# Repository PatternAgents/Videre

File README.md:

Videre
=============

PatternAgents Videre - LCD Shield with Cortex-M0

[  
*PatternAgents Videre*](http://www.patternagents.com/projects/Videre.html)

The PatternAgents Videre uses an ARM Cortex-M0 based Programmable System-on-Chip (PSoC4) 
to control a 16x2 Character LCD with color backlighting. The PSoC4  can read read inputs from sensors, 
switches, potentiometers, or other analog inputs and display those sensors directly on the LCD in
standalone mode. Or you can use it as an Arduino Shield, with either I2C,, UART, or SPI interface.

Features:

        16 Character x 2 Line Display

        Color LED Backlighting
	
        Selectable 3.3Volt or 5.0Volt Operation
	
        UART, I2C, SPI Interface Selectable
	
        Use as Arduino Shield or as a Standalone Display
	
        CapSense Slider Bar (optional)      

	Arduino Uno/Leonardo/Mega/Due Compatible Shield

You can read more about the PSoC4 Integrated Circuit used here : http://www.cypress.com/?mpn=CY8C4245AXI-483

[  
*Licensing CC BY-NC-SA 4.0*](http://creativecommons.org/licenses/by-nc-sa/4.0/)

PatternAgents uses the increasingly popular business model called "Dual Licensing" 
in which both the open source software distribution mechanism and traditional commercial software distribution models are combined.

Open Source Projects:        

If you are developing and distributing open source applications under the Creative Commons CC BY-NC-SA 4.0, 
as published by the Creative Commons Foundation, then you are free to use the PatternAgents hardware/software under the CC BY-NC-SA 4.0 license. 
Please note that CC BY-NC-SA 4.0 requires that all modifications to the original code as well as all Derivative Works 
must also be released under the terms of the CC BY-NC-SA 4.0 license.

Closed Source Projects:

If you are developing and distributing traditional closed source or commercial applications, 
you must purchase a PatternAgents commercial use license, 
which is specifically designed for users interested in retaining the proprietary status of their designs and code. 
All PatternAgents commercial licenses expressly supersede the CC BY-NC-SA 4.0 license. 
This means that when you license the PatternAgents software under a commercial license, 
you specifically do not use the software under the CC BY-NC-SA 4.0 license and therefore you are not subject to any of its terms.
        
If you would like to use our designs for your own personal or educational use, have at it! 

Our public design repository is available at <a href="https://github.com/patternagents">Github</a>.

If you would like to produce our designs for commercial use, or as products for sale, 
please contact us to arrange for a Commercial Use license. We have many other designs, 
as well as options and extras that are not released publicly. 
We will also customize designs, firmware, and software for a reasonable fee, just contact us to discuss your requirements.

THIS SOFTWARE IS PROVIDED BY THE CONTRIBUTORS "AS IS" AND WITHOUT ANY EXPRESS OR IMPLIED WARRANTIES, 
INCLUDING, BUT NOT LIMITED TO, THE IMPLIED WARRANTIES OF MERCHANTABILITY AND FITNESS FOR A PARTICULAR PURPOSE ARE DISCLAIMED. 
IN NO EVENT SHALL THE COPYRIGHT OWNER OR CONTRIBUTORS BE LIABLE FOR ANY DIRECT, INDIRECT, INCIDENTAL, SPECIAL, EXEMPLARY, 
OR CONSEQUENTIAL DAMAGES (INCLUDING, BUT NOT LIMITED TO, PROCUREMENT OF SUBSTITUTE GOODS OR SERVICES; LOSS OF USE, DATA, 
OR PROFITS; OR BUSINESS INTERRUPTION) HOWEVER CAUSED AND ON ANY THEORY OF LIABILITY, WHETHER IN CONTRACT, 
STRICT LIABILITY, OR TORT (INCLUDING NEGLIGENCE OR OTHERWISE) ARISING IN ANY WAY OUT OF THE USE OF THIS SOFTWARE, 
EVEN IF ADVISED OF THE POSSIBILITY OF SUCH DAMAGE. 

-------------------------------------------------------------------------------------------

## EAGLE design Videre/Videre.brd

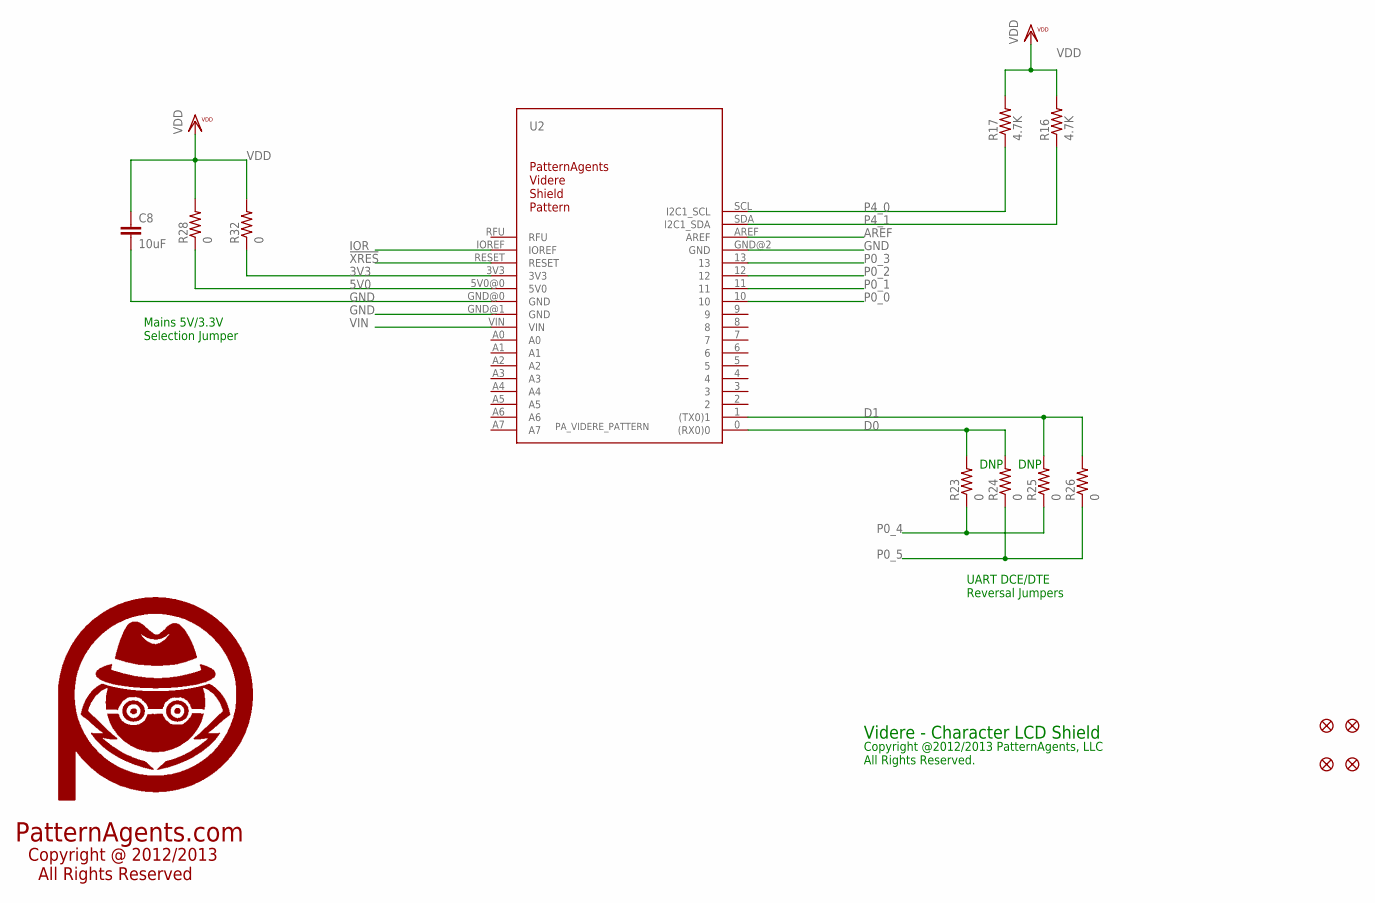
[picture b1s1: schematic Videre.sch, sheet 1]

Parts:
C8: 10uF; 1210
FID1, FID2, FID3, FID4: FIDUCIAL1.5X3; FIDUCIAL-1.5X3
R16, R17: 4.7K; R0603
R23, R24, R25, R26: 0; 0603-RES
R28, R32: 0; 0603-RES@1
U2: PA_VIDERE_PATTERN
U$3: PA_LOGO_SYMLARGE; PA_LOGO_AGENT_LRG_SYM

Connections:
3V3: R32.1, U2.3V3
5V0: R28.1, U2.5V0@0 (5V0)
!XRES: U2.RESET; also elsewhere on the board
AREF: U2.AREF
D0: R23.2, R24.2, U2.0 ((RX0)0)
D1: R25.2, R26.2, U2.1 ((TX0)1)
GND: C8.2, U2.GND@0 (GND), U2.GND@1 (GND), U2.GND@2 (GND); also elsewhere on the board
IOR: U2.IOREF
P0_0: U2.10; also elsewhere on the board
P0_1: U2.11; also elsewhere on the board
P0_2: U2.12; also elsewhere on the board
P0_3: U2.13; also elsewhere on the board
P0_4: R23.1, R25.1; also elsewhere on the board
P0_5: R24.1, R26.1; also elsewhere on the board
P4_0: R17.1, U2.SCL (I2C1_SCL); also elsewhere on the board
P4_1: R16.1, U2.SDA (I2C1_SDA); also elsewhere on the board
RFU: U2.RFU
VDD: C8.1, R16.2, R17.2, R28.2, R32.2; also elsewhere on the board
VIN: U2.VIN; also elsewhere on the board

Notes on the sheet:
DNP
UART DCE/DTE Reversal Jumpers
Mains 5V/3.3V Selection Jumper
PatternAgents.com
Copyright @ 2012/2013 All Rights Reserved
Videre - Character LCD Shield
Copyright @2012/2013 PatternAgents, LLC All Rights Reserved.

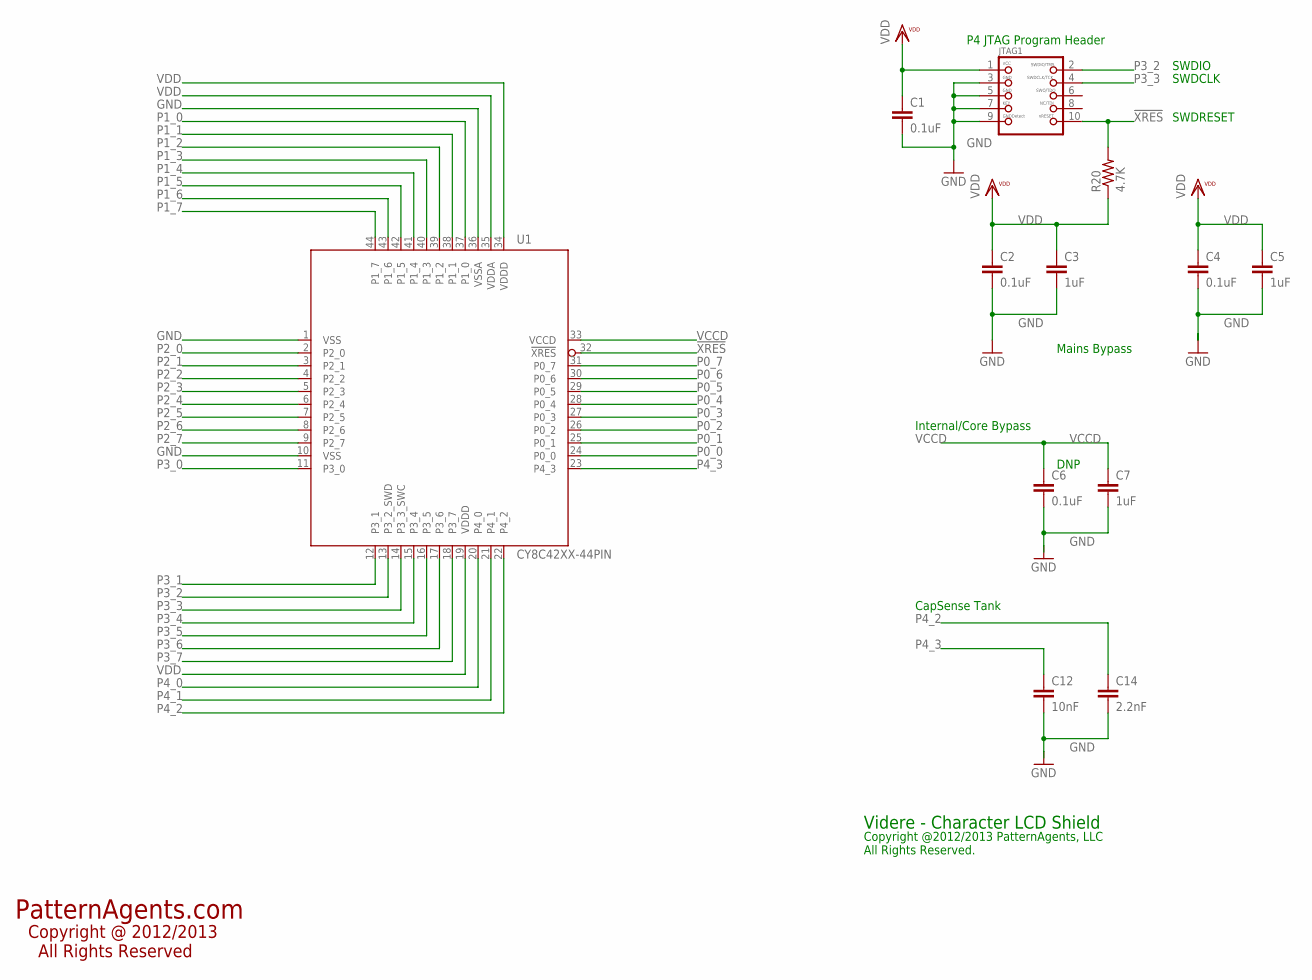
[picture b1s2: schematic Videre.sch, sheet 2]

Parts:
C1, C2, C4, C6: 0.1uF; 0603-CAP
C3, C5, C7: 1uF; 0603-CAP
C12: 10nF; 0603-CAP
C14: 2.2nF; 0603-CAP
JTAG1: JTAG-CORTEXM3; 2X05_1.27MM_SMT
R20: 4.7K; 0603-RES
U1: CY8C42XX-44PIN; TQFP-10X10-44

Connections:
!XRES: JTAG1.10, R20.2, U1.32 (!XRES); also elsewhere on the board
GND: C1.2, C2.2, C3.2, C4.2, C5.2, C6.2, C7.2, C12.2, C14.2, JTAG1.3, JTAG1.5, JTAG1.7, JTAG1.9, U1.1 (VSS), U1.10 (VSS), U1.36 (VSSA); also elsewhere on the board
P0_0: U1.24 (P0_0); also elsewhere on the board
P0_1: U1.25 (P0_1); also elsewhere on the board
P0_2: U1.26 (P0_2); also elsewhere on the board
P0_3: U1.27 (P0_3); also elsewhere on the board
P0_4: U1.28 (P0_4); also elsewhere on the board
P0_5: U1.29 (P0_5); also elsewhere on the board
P0_6: U1.30 (P0_6); also elsewhere on the board
P0_7: U1.31 (P0_7); also elsewhere on the board
P1_0: U1.37 (P1_0); also elsewhere on the board
P1_1: U1.38 (P1_1); also elsewhere on the board
P1_2: U1.39 (P1_2); also elsewhere on the board
P1_3: U1.40 (P1_3); also elsewhere on the board
P1_4: U1.41 (P1_4); also elsewhere on the board
P1_5: U1.42 (P1_5); also elsewhere on the board
P1_6: U1.43 (P1_6); also elsewhere on the board
P1_7: U1.44 (P1_7); also elsewhere on the board
P2_0: U1.2 (P2_0); also elsewhere on the board
P2_1: U1.3 (P2_1); also elsewhere on the board
P2_2: U1.4 (P2_2); also elsewhere on the board
P2_3: U1.5 (P2_3); also elsewhere on the board
P2_4: U1.6 (P2_4); also elsewhere on the board
P2_5: U1.7 (P2_5); also elsewhere on the board
P2_6: U1.8 (P2_6); also elsewhere on the board
P2_7: U1.9 (P2_7); also elsewhere on the board
P3_0: U1.11 (P3_0); also elsewhere on the board
P3_1: U1.12 (P3_1); also elsewhere on the board
P3_2: JTAG1.2, U1.13 (P3_2_SWD)
P3_3: JTAG1.4, U1.14 (P3_3_SWC)
P3_4: U1.15 (P3_4); also elsewhere on the board
P3_5: U1.16 (P3_5); also elsewhere on the board
P3_6: U1.17 (P3_6); also elsewhere on the board
P3_7: U1.18 (P3_7); also elsewhere on the board
P4_0: U1.20 (P4_0); also elsewhere on the board
P4_1: U1.21 (P4_1); also elsewhere on the board
P4_2: C14.1, U1.22 (P4_2)
P4_3: C12.1, U1.23 (P4_3)
VCCD: C6.1, C7.1, U1.33 (VCCD)
VDD: C1.1, C2.1, C3.1, C4.1, C5.1, JTAG1.1, R20.1, U1.19 (VDDD), U1.34 (VDDD), U1.35 (VDDA); also elsewhere on the board

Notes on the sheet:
SWDIO
SWDCLK
SWDRESET
P4 JTAG Program Header
DNP
CapSense Tank
Internal/Core Bypass
Mains Bypass
Videre - Character LCD Shield
Copyright @2012/2013 PatternAgents, LLC All Rights Reserved.
PatternAgents.com
Copyright @ 2012/2013 All Rights Reserved

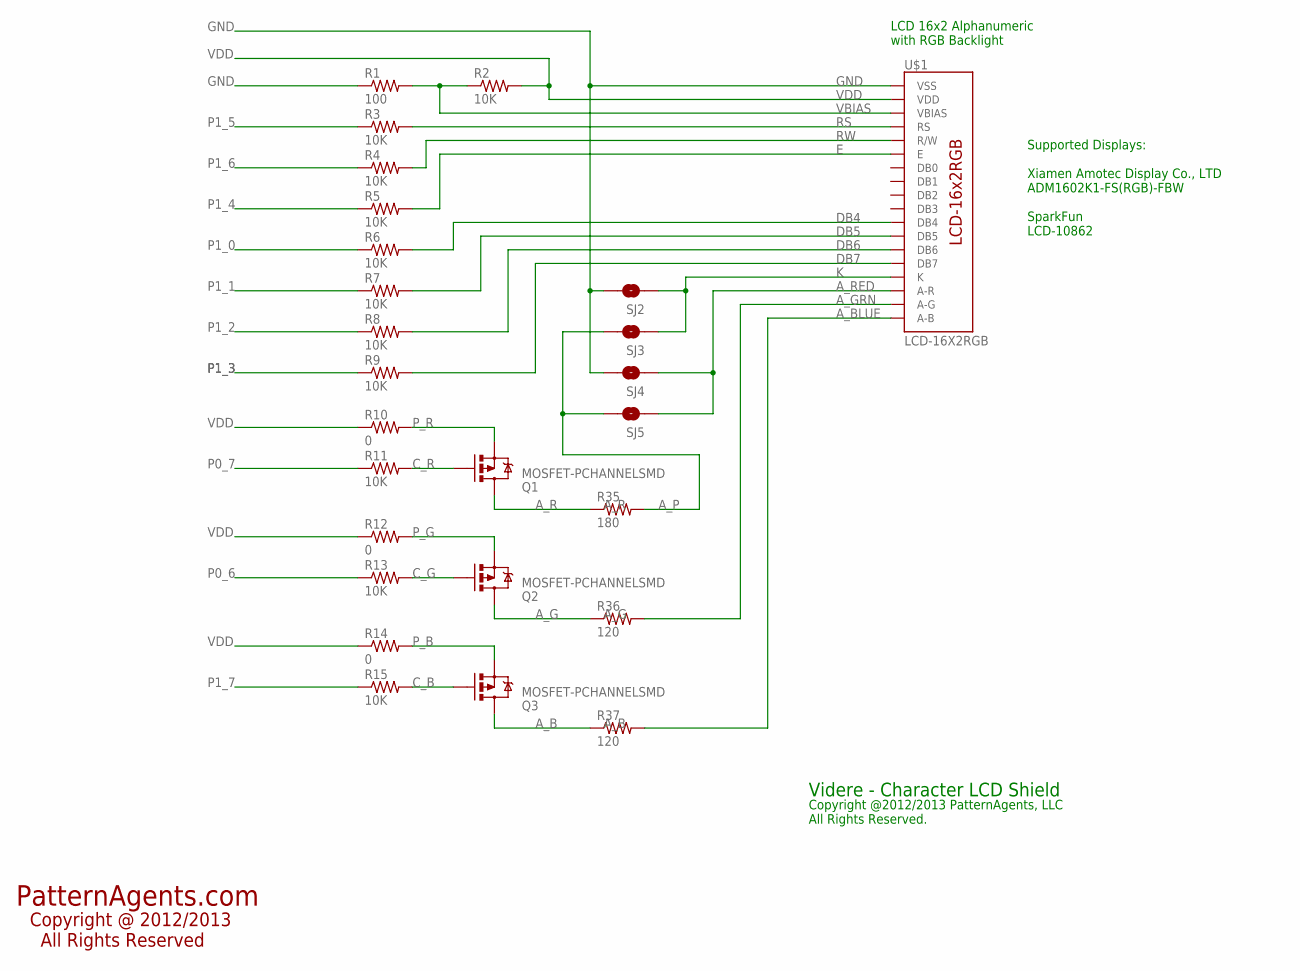
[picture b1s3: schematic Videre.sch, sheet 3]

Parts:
Q1, Q2, Q3: MOSFET-PCHANNELSMD; SOT23-3
R1: 100; 0603-RES
R2, R3, R4, R5, R6, R7, R8, R9, R11, R13, R15: 10K; 0603-RES
R10, R12, R14: 0; 0603-RES
R35: 180; 0603-RES
R36, R37: 120; 0603-RES
SJ2, SJ3, SJ4, SJ5: SOLDERJUMPERNO; SJ_2S-NO
U$1: LCD-16X2RGB

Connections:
A_B: Q3.3 (D), R37.1
A_BLUE: R37.2, U$1.18 (A-B)
A_G: Q2.3 (D), R36.1
A_GRN: R36.2, U$1.17 (A-G)
A_P: R35.2, SJ3.2, SJ5.2
A_R: Q1.3 (D), R35.1
A_RED: SJ4.1, SJ5.1, U$1.16 (A-R)
C_B: Q3.1 (G), R15.2
C_G: Q2.1 (G), R13.2
C_R: Q1.1 (G), R11.2
DB4: R6.2, U$1.11 (DB4)
DB5: R7.2, U$1.12 (DB5)
DB6: R8.2, U$1.13 (DB6)
DB7: R9.2, U$1.14 (DB7)
E: R5.2, U$1.6 (E)
GND: R1.1, SJ2.2, SJ4.2, U$1.1 (VSS); also elsewhere on the board
K: SJ2.1, SJ3.1, U$1.15 (K)
P0_6: R13.1; also elsewhere on the board
P0_7: R11.1; also elsewhere on the board
P1_0: R6.1; also elsewhere on the board
P1_1: R7.1; also elsewhere on the board
P1_2: R8.1; also elsewhere on the board
P1_3: R9.1; also elsewhere on the board
P1_4: R5.1; also elsewhere on the board
P1_5: R3.1; also elsewhere on the board
P1_6: R4.1; also elsewhere on the board
P1_7: R15.1; also elsewhere on the board
P_B: Q3.2 (S), R14.2
P_G: Q2.2 (S), R12.2
P_R: Q1.2 (S), R10.2
RS: R3.2, U$1.4 (RS)
RW: R4.2, U$1.5 (R/W)
VBIAS: R1.2, R2.1, U$1.3 (VBIAS)
VDD: R2.2, R10.1, R12.1, R14.1, U$1.2 (VDD); also elsewhere on the board

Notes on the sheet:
LCD 16x2 Alphanumeric with RGB Backlight
Supported Displays: Xiamen Amotec Display Co., LTD ADM1602K1-FS(RGB)-FBW SparkFun LCD-10862
Videre - Character LCD Shield
Copyright @2012/2013 PatternAgents, LLC All Rights Reserved.
PatternAgents.com
Copyright @ 2012/2013 All Rights Reserved

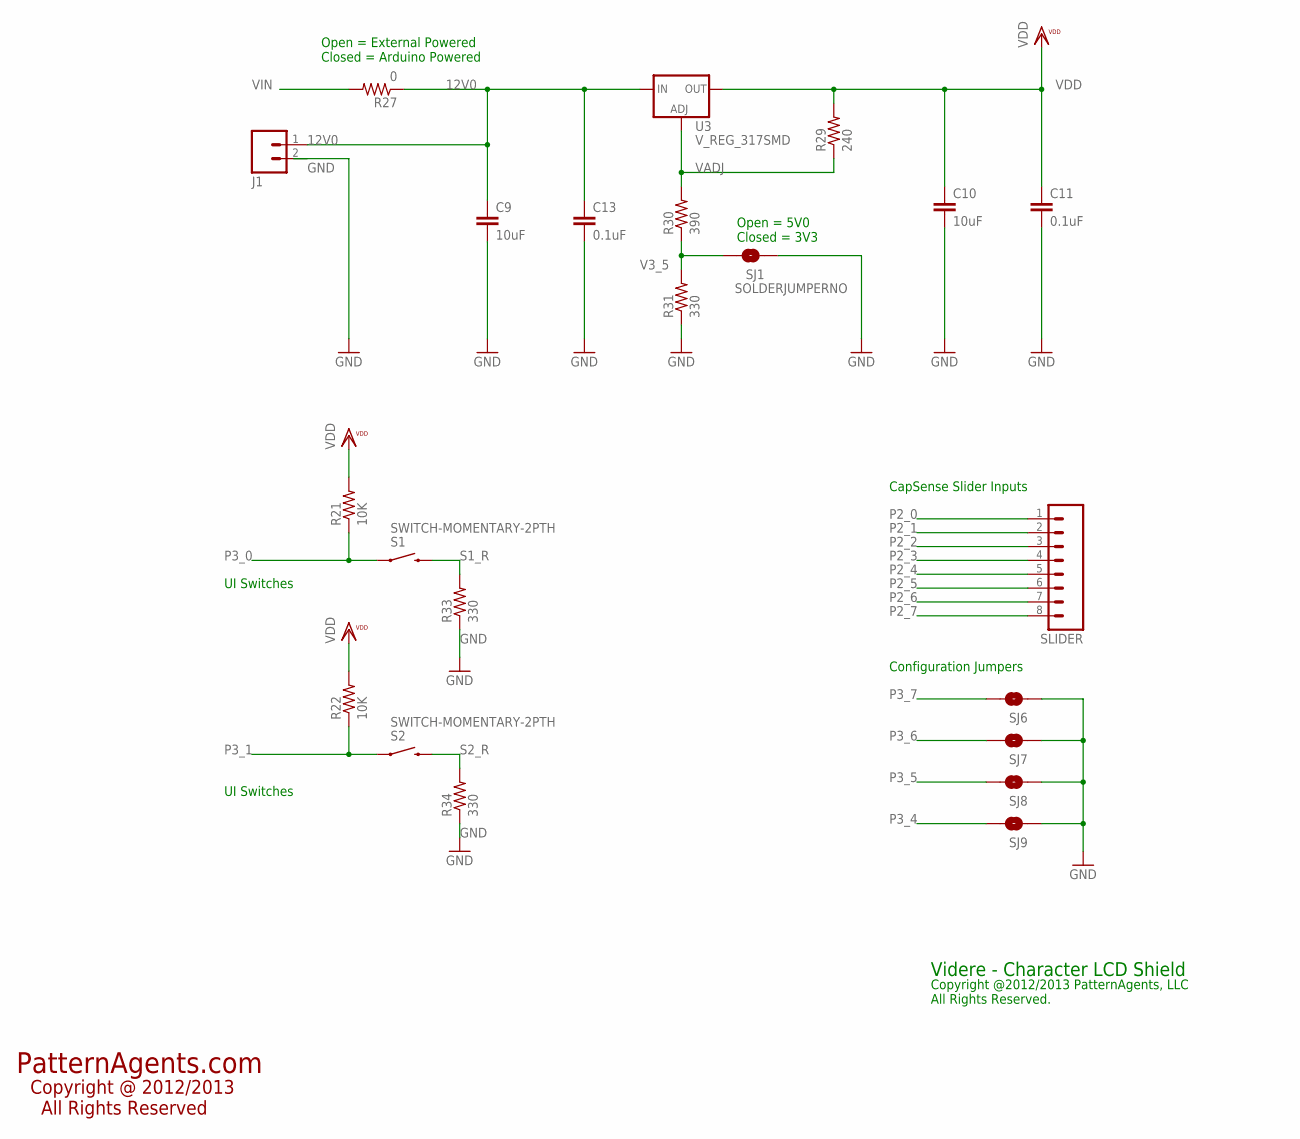
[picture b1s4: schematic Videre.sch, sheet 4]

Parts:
C9, C10: 10uF; 1210
C11, C13: 0.1uF; 0603-CAP
J1: M02PTH; 1X02
R21, R22: 10K; 0603-RES
R27: 0; 0603-RES
R29: 240; R0603
R30: 390; R0603
R31, R33, R34: 330; R0603
S1, S2: SWITCH-MOMENTARY-2PTH; TACTILE-PTH
SJ1, SJ6, SJ7, SJ8, SJ9: SOLDERJUMPERNO; SJ_2S-NO
SLIDER: M081X08; 1X08
U3: V_REG_317SMD; SOT223

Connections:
12V0: C9.1, C13.1, J1.1, R27.1, U3.3 (IN)
GND: C9.2, C10.2, C11.2, C13.2, J1.2, R31.1, R33.1, R34.1, SJ1.1, SJ6.1, SJ7.1, SJ8.1, SJ9.1; also elsewhere on the board
P2_0: SLIDER.1; also elsewhere on the board
P2_1: SLIDER.2; also elsewhere on the board
P2_2: SLIDER.3; also elsewhere on the board
P2_3: SLIDER.4; also elsewhere on the board
P2_4: SLIDER.5; also elsewhere on the board
P2_5: SLIDER.6; also elsewhere on the board
P2_6: SLIDER.7; also elsewhere on the board
P2_7: SLIDER.8; also elsewhere on the board
P3_0: R21.1, S1.1; also elsewhere on the board
P3_1: R22.1, S2.1; also elsewhere on the board
P3_4: SJ9.2; also elsewhere on the board
P3_5: SJ8.2; also elsewhere on the board
P3_6: SJ7.2; also elsewhere on the board
P3_7: SJ6.2; also elsewhere on the board
S1_R: R33.2, S1.3 (2)
S2_R: R34.2, S2.3 (2)
V3_5: R30.1, R31.2, SJ1.2
VADJ: R29.1, R30.2, U3.1 (ADJ)
VDD: C10.1, C11.1, R21.2, R22.2, R29.2, U3.2 (OUT); also elsewhere on the board
VIN: R27.2; also elsewhere on the board

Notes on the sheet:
Open = 5V0 Closed = 3V3
Open = External Powered Closed = Arduino Powered
CapSense Slider Inputs
Configuration Jumpers
UI Switches
Videre - Character LCD Shield
Copyright @2012/2013 PatternAgents, LLC All Rights Reserved.
PatternAgents.com
Copyright @ 2012/2013 All Rights Reserved

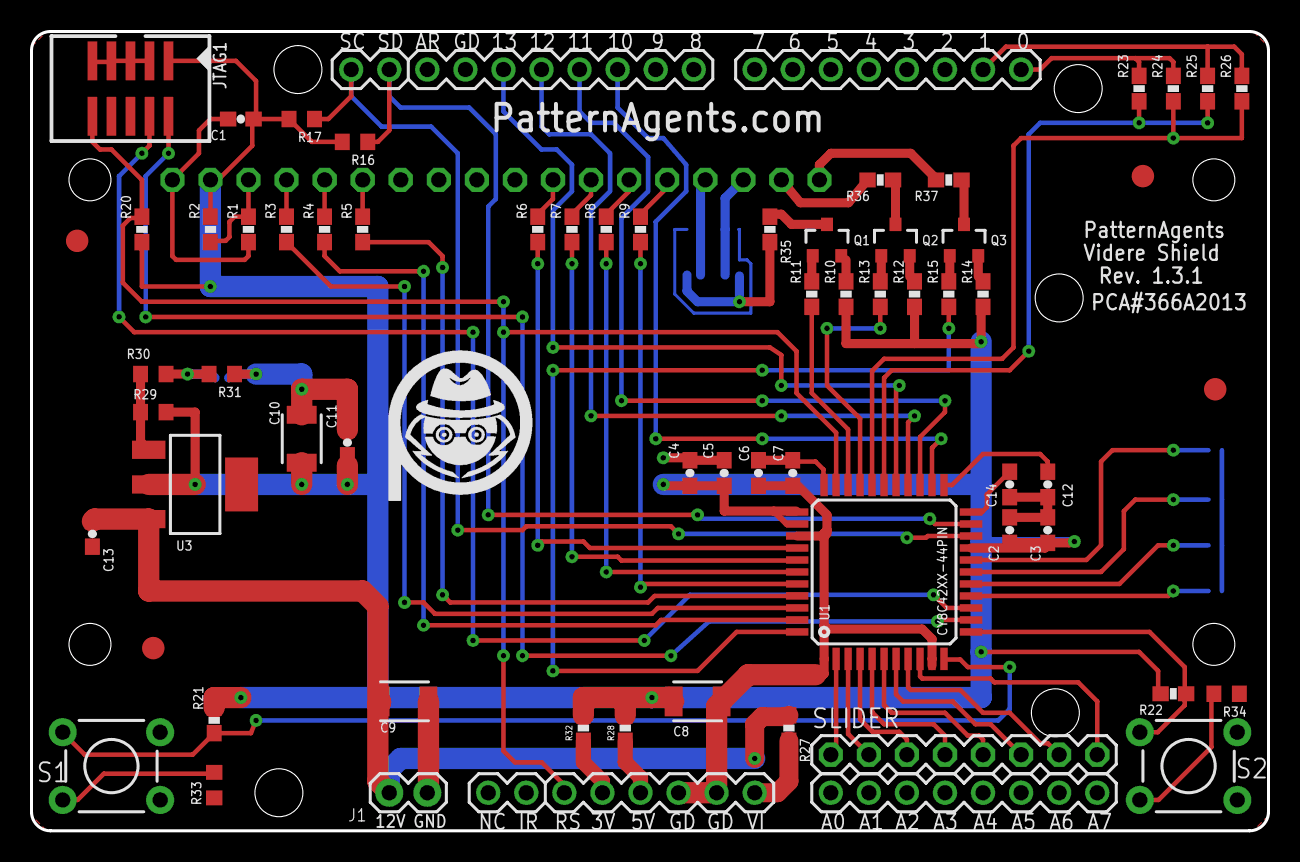
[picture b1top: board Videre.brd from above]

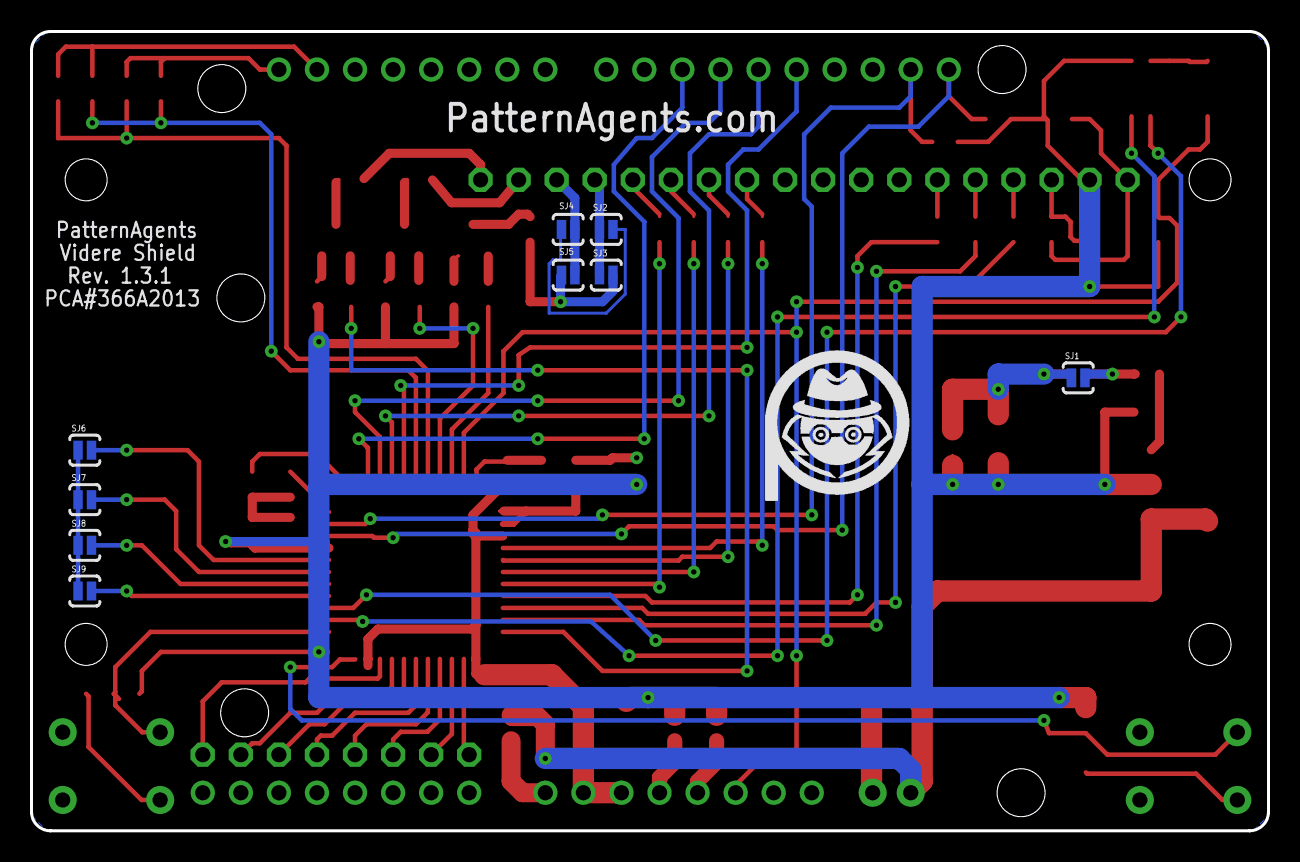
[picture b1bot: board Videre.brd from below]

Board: 2 copper layers, 82.5 x 53.3 mm, 76 parts (10 on the bottom side), 72 nets.

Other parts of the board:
U$2: PA_LOGO_SYMLARGE; PA_LOGO_AGENT_LRG_SYM

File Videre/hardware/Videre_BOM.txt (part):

Partlist  at 6/29/2013 11:25:48 AM eagle/PatternAgents/Arduino/Videre/Videre/Videre.sch

Part   Value                 Device                Package               Description                                                     
C1     0.1uF                 CAP0603-CAP           0603-CAP              Capacitor                                                       
C2     0.1uF                 CAP0603-CAP           0603-CAP              Capacitor                                                       
C3     1uF                   CAP0603-CAP           0603-CAP              Capacitor                                                       
C4     0.1uF                 CAP0603-CAP           0603-CAP              Capacitor                                                       
C5     1uF                   CAP0603-CAP           0603-CAP              Capacitor                                                       
C6     0.1uF                 CAP0603-CAP           0603-CAP              Capacitor                                                       
C7     1uF                   CAP0603-CAP           0603-CAP              Capacitor                                                       
C8     10uF                  CAP1210               1210                  Capacitor                                                       
C9     10uF                  CAP1210               1210                  Capacitor                                                       
C10    10uF                  CAP1210               1210                  Capacitor                                                       
C11    0.1uF                 CAP0603-CAP           0603-CAP              Capacitor                                                       
C12    10nF                  CAP0603-CAP           0603-CAP              Capacitor                                                       
C13    0.1uF                 CAP0603-CAP           0603-CAP              Capacitor                                                       
C14    2.2nF                 CAP0603-CAP           0603-CAP              Capacitor                                                       
J1                           M02PTH                1X02                  Header 2                                                        
JTAG1                        JTAG-CORTEXM3         2X05_1.27MM_SMT       JTAG Programming Connector                                      
Q1     MOSFET-PCHANNELSMD    MOSFET-PCHANNELSMD    SOT23-3               Generic PMOSFET                                                 
Q2     MOSFET-PCHANNELSMD    MOSFET-PCHANNELSMD    SOT23-3               Generic PMOSFET                                                 
Q3     MOSFET-PCHANNELSMD    MOSFET-PCHANNELSMD    SOT23-3               Generic PMOSFET                                                 
R1     100                   RESISTOR_SFE0603-RES  0603-RES              Resistor                                                        
R2     10K                   RESISTOR_SFE0603-RES  0603-RES              Resistor                                                        
R3     10K                   RESISTOR_SFE0603-RES  0603-RES              Resistor                                                        
R4     10K                   RESISTOR_SFE0603-RES  0603-RES              Resistor                                                        
R5     10K                   RESISTOR_SFE0603-RES  0603-RES              Resistor                                                        
R6     10K                   RESISTOR_SFE0603-RES  0603-RES              Resistor                                                        
R7     10K                   RESISTOR_SFE0603-RES  0603-RES              Resistor                                                        
R8     10K                   RESISTOR_SFE0603-RES  0603-RES              Resistor                                                        
R9     10K                   RESISTOR_SFE0603-RES  0603-RES              Resistor                                                        
R10    0                     RESISTOR_SFE0603-RES  0603-RES              Resistor                                                        
R11    10K                   RESISTOR_SFE0603-RES  0603-RES              Resistor                                                        
R12    0                     RESISTOR_SFE0603-RES  0603-RES              Resistor                                                        
R13    10K                   RESISTOR_SFE0603-RES  0603-RES              Resistor                                                        
R14    0                     RESISTOR_SFE0603-RES  0603-RES              Resistor                                                        
R15    10K                   RESISTOR_SFE0603-RES  0603-RES              Resistor                                                        
R16    4.7K                  RESISTORR0603         R0603                 RESISTOR, American symbol                                       
R17    4.7K                  RESISTORR0603         R0603                 RESISTOR, American symbol                                       
R20    4.7K                  RESISTOR_SFE0603-RES  0603-RES              Resistor                                                        
R21    10K                   RESISTOR_SFE0603-RES  0603-RES              Resistor                                                        
R22    10K                   RESISTOR_SFE0603-RES  0603-RES              Resistor                                                        
R23    0                     RESISTOR_SFE0603-RES  0603-RES              Resistor                                                        
R24    0                     RESISTOR_SFE0603-RES  0603-RES              Resistor                                                        
R25    0                     RESISTOR_SFE0603-RES  0603-RES              Resistor                                                        
R26    0                     RESISTOR_SFE0603-RES  0603-RES              Resistor                                                        
R27    0                     RESISTOR_SFE0603-RES  0603-RES              Resistor                                                        
R28    0                     RESISTOR_SFE0603-RES  0603-RES              Resistor                                                        
R29    240                   RESISTORR0603         R0603                 RESISTOR, American symbol                                       
R30    390                   RESISTORR0603         R0603                 RESISTOR, American symbol                                       
R31    330                   RESISTORR0603         R0603                 RESISTOR, American symbol                                       
R32    0                     RESISTOR_SFE0603-RES  0603-RES              Resistor                                                        
R33    330                   RESISTORR0603         R0603                 RESISTOR, American symbol                                       
R34    330                   RESISTORR0603         R0603                 RESISTOR, American symbol                                       
R35    180                   RESISTOR_SFE0603-RES  0603-RES              Resistor                                                        
R36    120                   RESISTOR_SFE0603-RES  0603-RES              Resistor                                                        
R37    120                   RESISTOR_SFE0603-RES  0603-RES              Resistor                                                        
S1     SWITCH-MOMENTARY-2PTH SWITCH-MOMENTARY-2PTH TACTILE-PTH           Various NO switches- pushbuttons, reed, etc                     
S2     SWITCH-MOMENTARY-2PTH SWITCH-MOMENTARY-2PTH TACTILE-PTH           Various NO switches- pushbuttons, reed, etc                     
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
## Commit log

2013-07-18 initial project creation
2013-07-18 link fixes
2013-07-23 smaller png file sizes
2013-11-17 Videre - Initial Production Release
    Eagle Cad Schematics and Layout
    EagleUp 3D Models
    Gerber Files and BOM
    Images and Rendered Models
2013-12-23 Move Licensing to CC 4.0 for consistancy

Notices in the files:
parts and their libraries:
SparkFun-DiscreteSemi: Licensing: CC v3.0 Share-Alike You are welcome to use this library for commercial purposes.
PatternAgents-Cypress: License : http://creativecommons.org/licenses/by-sa/3.0
(Creative Commons 3.0)
PatternAgents-Boards: License : http://creativecommons.org/licenses/by-sa/2.5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
